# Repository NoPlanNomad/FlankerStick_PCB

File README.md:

# FlankerStick_PCBs
 
PCB's designed for my Flanker Style DIY Hotas stick.

https://cults3d.com/en/3d-model/game/flanker-style-stick

https://www.cgtrader.com/3d-print-models/hobby-diy/mechanical-parts/flanker-style-stick

# BOM
## GripLogic_FreeJoy
|quantaty | Type:Value      |Footprint|
|---------|-----------------|---------|
|2        |Capacitor : 0.1uF|0805     |
|9        |Resistor  : 1K   |0805     |
|2        |74HC165          |TSSOP-16 |
|2        |JST_XH:B5B-XH-A  |P2.50 mm |
|4        |JST_XH:B2B-XH-A  |P2.50 mm |
|2        |JST_XH:B7B-XH-A  |P2.50 mm |

## HeadLogic_FreeJoy
|quantaty | Type:Value      |Footprint|
|---------|-----------------|---------|
|3        |Capacitor : 0.1uF|0805     |
|24       |Resitor   : 1K   |0805     |
|3        |74HC165          |TSSOP-16 |
|4        |JST_XH:B7B-XH-A  |P2.50 mm |
|4        |JST_XH:B2B-XH-A  |P2.50 mm |
|1        |JST_XH:B5B-XH-A  |P2.50 mm |

## Breaklever_FreeJoy
|quantaty | Type:Value      |Footprint|
|---------|-----------------|---------|
|1        |SS495A           |TH       |
|1        |MCP3201          |SOIC 3.9 |
|1        |JST_XH:B5B-XH-A  |P2.50 mm |

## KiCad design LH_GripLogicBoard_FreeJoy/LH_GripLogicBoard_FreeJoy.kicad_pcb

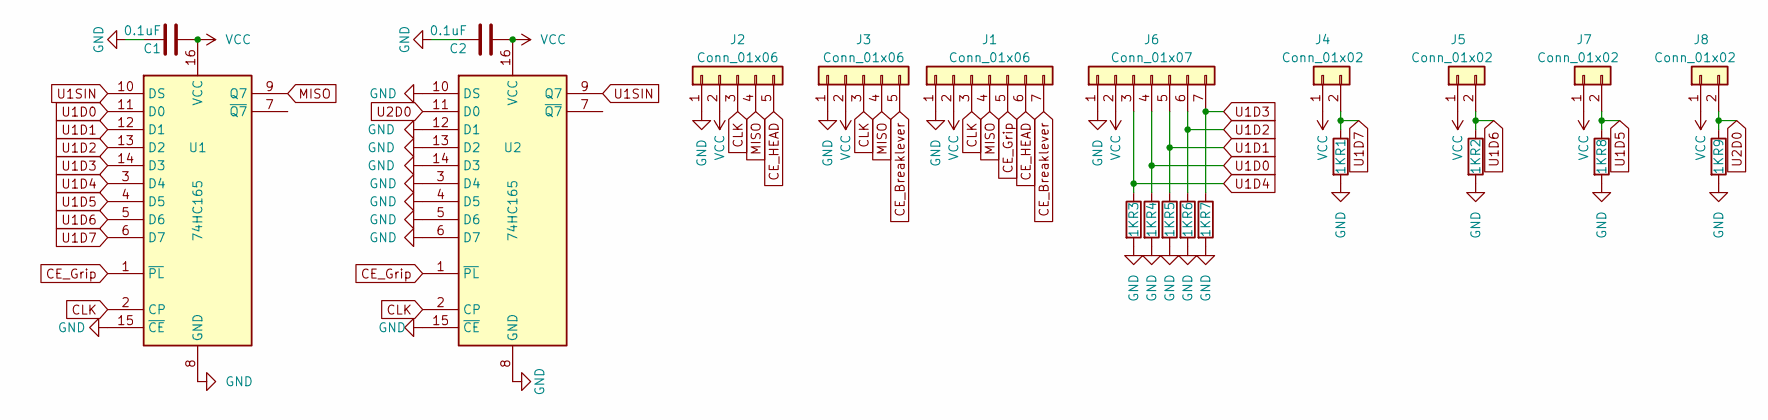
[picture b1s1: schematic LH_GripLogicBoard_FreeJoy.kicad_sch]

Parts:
C1, C2: 0.1uF; C_0805_2012Metric_Pad1.18x1.45mm_HandSolder
J1: Conn_01x06; JST_XH_B7B-XH-A_1x07_P2.50mm_Vertical
J2, J3: Conn_01x06; JST_XH_B5B-XH-A_1x05_P2.50mm_Vertical
J4, J5, J7, J8: Conn_01x02; JST_XH_B2B-XH-A_1x02_P2.50mm_Vertical
J6: Conn_01x07; JST_XH_B7B-XH-A_1x07_P2.50mm_Vertical
R1, R2, R3, R4, R5, R6, R7, R8, R9: 1K; R_0805_2012Metric_Pad1.20x1.40mm_HandSolder
U1, U2: 74HC165; TSSOP-16_4.4x5mm_P0.65mm

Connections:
CE_Breaklever: J1.7, J3.5
CE_Grip: J1.5, U1.1 (~PL), U2.1 (~PL)
CE_HEAD: J1.6, J2.5
CLK: J1.3, J2.3, J3.3, U1.2 (CP), U2.2 (CP)
GND: C1.1, C2.1, J1.1, J2.1, J3.1, J6.1, R1.2, R2.2, R3.2, R4.2, R5.2, R6.2, R7.2, R8.2, R9.2, U1.8 (GND), U1.15 (~CE), U2.3 (D4), U2.4 (D5), U2.5 (D6), U2.6 (D7), U2.8 (GND), U2.10 (DS), U2.12 (D1), U2.13 (D2), U2.14 (D3), U2.15 (~CE)
MISO: J1.4, J2.4, J3.4, U1.9 (Q7)
U1D0: J6.4, R4.1, U1.11 (D0)
U1D1: J6.5, R5.1, U1.12 (D1)
U1D2: J6.6, R6.1, U1.13 (D2)
U1D3: J6.7, R7.1, U1.14 (D3)
U1D4: J6.3, R3.1, U1.3 (D4)
U1D5: J7.2, R8.1, U1.4 (D5)
U1D6: J5.2, R2.1, U1.5 (D6)
U1D7: J4.2, R1.1, U1.6 (D7)
U1SIN: U1.10 (DS), U2.9 (Q7)
U2D0: J8.2, R9.1, U2.11 (D0)
VCC: C1.2, C2.2, J1.2, J2.2, J3.2, J4.1, J5.1, J6.2, J7.1, J8.1, U1.16 (VCC), U2.16 (VCC)

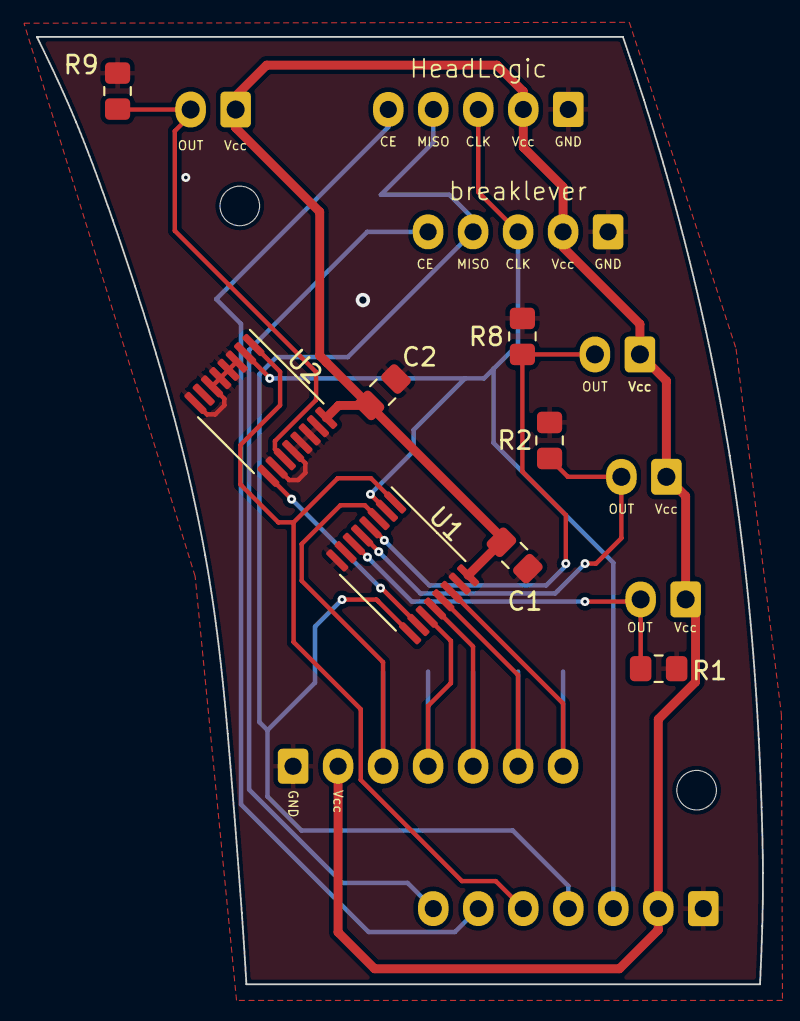
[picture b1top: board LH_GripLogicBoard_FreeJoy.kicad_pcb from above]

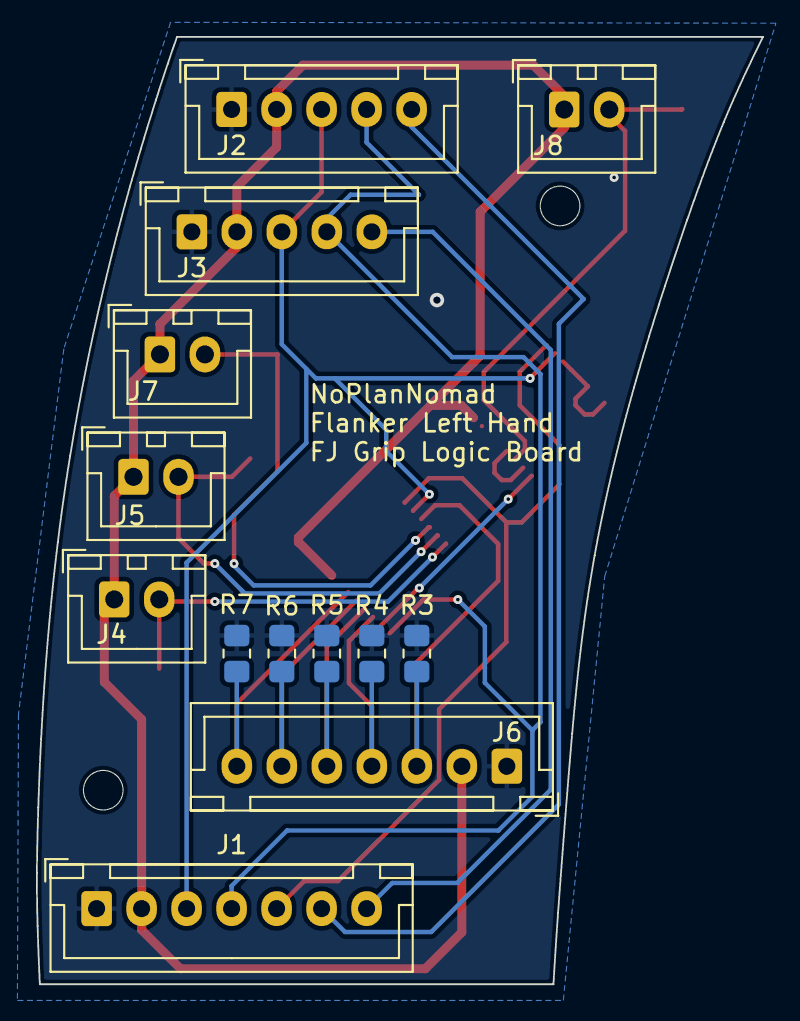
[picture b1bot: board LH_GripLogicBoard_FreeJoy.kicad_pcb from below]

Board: 2 copper layers, 40.3 x 52.6 mm, 21 parts (13 on the bottom side), 17 nets.

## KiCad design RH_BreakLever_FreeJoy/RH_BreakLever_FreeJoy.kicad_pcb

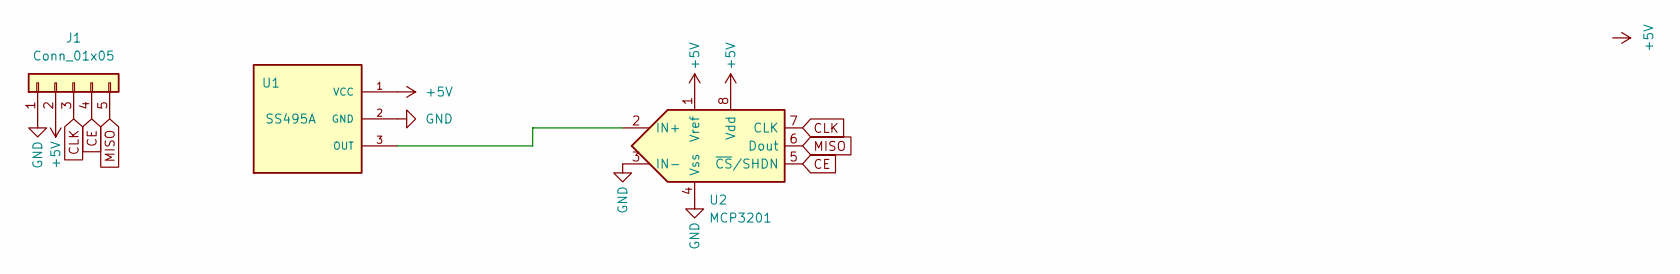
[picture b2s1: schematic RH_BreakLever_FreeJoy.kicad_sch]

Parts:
J1: Conn_01x05; JST_XH_B5B-XH-A_1x05_P2.50mm_Vertical
U1: SS495A; SS49E-T2; PARTREV Issue 3
U2: MCP3201; SOIC-8_3.9x4.9mm_P1.27mm

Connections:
+5V: J1.2, U1.1 (VCC), U2.1 (Vref), U2.8 (Vdd)
CE: J1.4, U2.5 (~CS/SHDN)
CLK: J1.3, U2.7 (CLK)
GND: J1.1, U1.2 (GND), U2.3 (IN-), U2.4 (Vss)
MISO: J1.5, U2.6 (Dout)
unnamed: U1.3 (OUT), U2.2 (IN+)

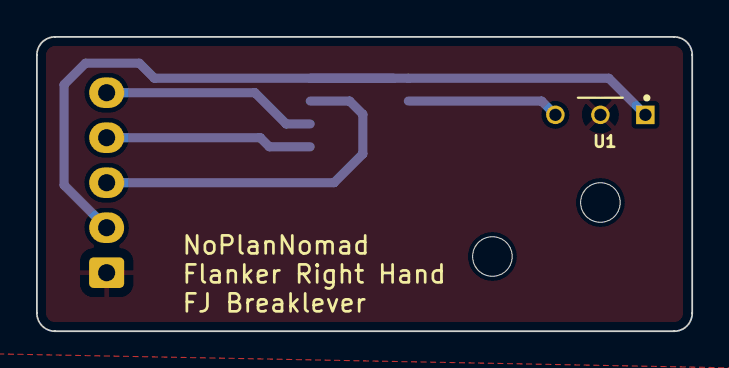
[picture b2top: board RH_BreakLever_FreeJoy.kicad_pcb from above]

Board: 2 copper layers, 36.4 x 16.3 mm, 5 parts (1 on the bottom side), 6 nets.

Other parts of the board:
M1, M2: MountingHole_2.2mm_M2

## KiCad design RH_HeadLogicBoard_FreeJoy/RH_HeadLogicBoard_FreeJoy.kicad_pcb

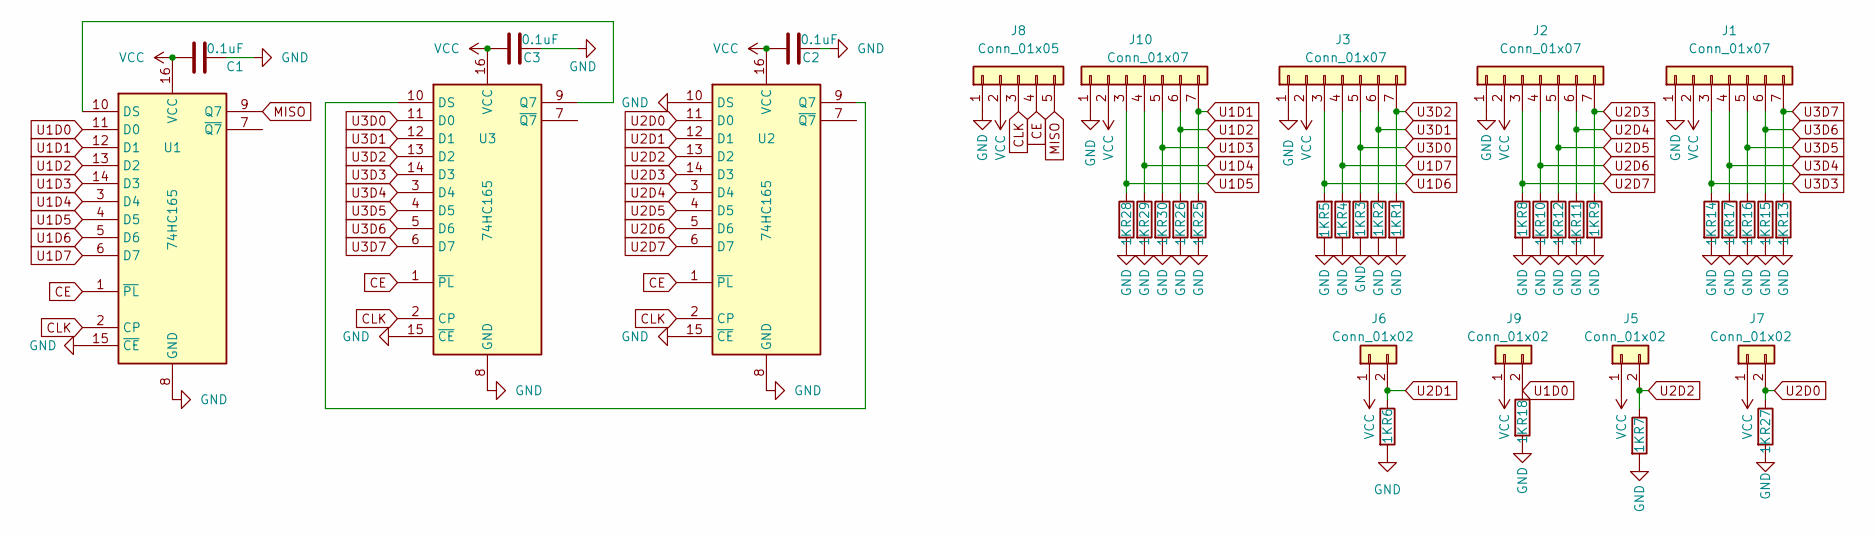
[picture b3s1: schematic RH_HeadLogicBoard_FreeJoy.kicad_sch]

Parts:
C1, C2, C3: 0.1uF; C_0805_2012Metric_Pad1.18x1.45mm_HandSolder
J1, J2, J3, J10: Conn_01x07; JST_XH_B7B-XH-A_1x07_P2.50mm_Vertical
J5, J6, J7, J9: Conn_01x02; JST_XH_B2B-XH-A_1x02_P2.50mm_Vertical
J8: Conn_01x05; JST_XH_B5B-XH-A_1x05_P2.50mm_Vertical
R1, R2, R3, R4, R5, R6, R7, R8, R9, R10, R11, R12, R13, R14, R15, R16, R17, R18, R25, R26, R27, R28, R29, R30: 1K; R_0805_2012Metric_Pad1.20x1.40mm_HandSolder
U1, U2, U3: 74HC165; TSSOP-16_4.4x5mm_P0.65mm

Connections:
+5V: C1.1, C2.1, C3.1, J1.2, J2.2, J3.2, J5.1, J6.1, J7.1, J8.2, J9.1, J10.2, U1.16 (VCC), U2.16 (VCC), U3.16 (VCC)
CE: J8.4, U1.1 (~PL), U2.1 (~PL), U3.1 (~PL)
CLK: J8.3, U1.2 (CP), U2.2 (CP), U3.2 (CP)
GND: C1.2, C2.2, C3.2, J1.1, J2.1, J3.1, J8.1, J10.1, R1.2, R2.2, R3.2, R4.1, R5.1, R6.2, R7.2, R8.2, R9.2, R10.2, R11.2, R12.2, R13.2, R14.2, R15.2, R16.2, R17.2, R18.2, R25.2, R26.2, R27.2, R28.2, R29.2, R30.2, U1.8 (GND), U1.15 (~CE), U2.8 (GND), U2.10 (DS), U2.15 (~CE), U3.8 (GND), U3.15 (~CE)
MISO: J8.5, U1.9 (Q7)
unnamed: U1.10 (DS), U3.9 (Q7)
unnamed: U2.9 (Q7), U3.10 (DS)
U1D0: J9.2, R18.1, U1.11 (D0)
U1D1: J10.7, R25.1, U1.12 (D1)
U1D2: J10.6, R26.1, U1.13 (D2)
U1D3: J10.5, R30.1, U1.14 (D3)
U1D4: J10.4, R29.1, U1.3 (D4)
U1D5: J10.3, R28.1, U1.4 (D5)
U1D6: J3.3, R5.2, U1.5 (D6)
U1D7: J3.4, R4.2, U1.6 (D7)
U2D0: J7.2, R27.1, U2.11 (D0)
U2D1: J6.2, R6.1, U2.12 (D1)
U2D2: J5.2, R7.1, U2.13 (D2)
U2D3: J2.7, R9.1, U2.14 (D3)
U2D4: J2.6, R11.1, U2.3 (D4)
U2D5: J2.5, R12.1, U2.4 (D5)
U2D6: J2.4, R10.1, U2.5 (D6)
U2D7: J2.3, R8.1, U2.6 (D7)
U3D0: J3.5, R3.1, U3.11 (D0)
U3D1: J3.6, R2.1, U3.12 (D1)
U3D2: J3.7, R1.1, U3.13 (D2)
U3D3: J1.3, R14.1, U3.14 (D3)
U3D4: J1.4, R17.1, U3.3 (D4)
U3D5: J1.5, R16.1, U3.4 (D5)
U3D6: J1.6, R15.1, U3.5 (D6)
U3D7: J1.7, R13.1, U3.6 (D7)

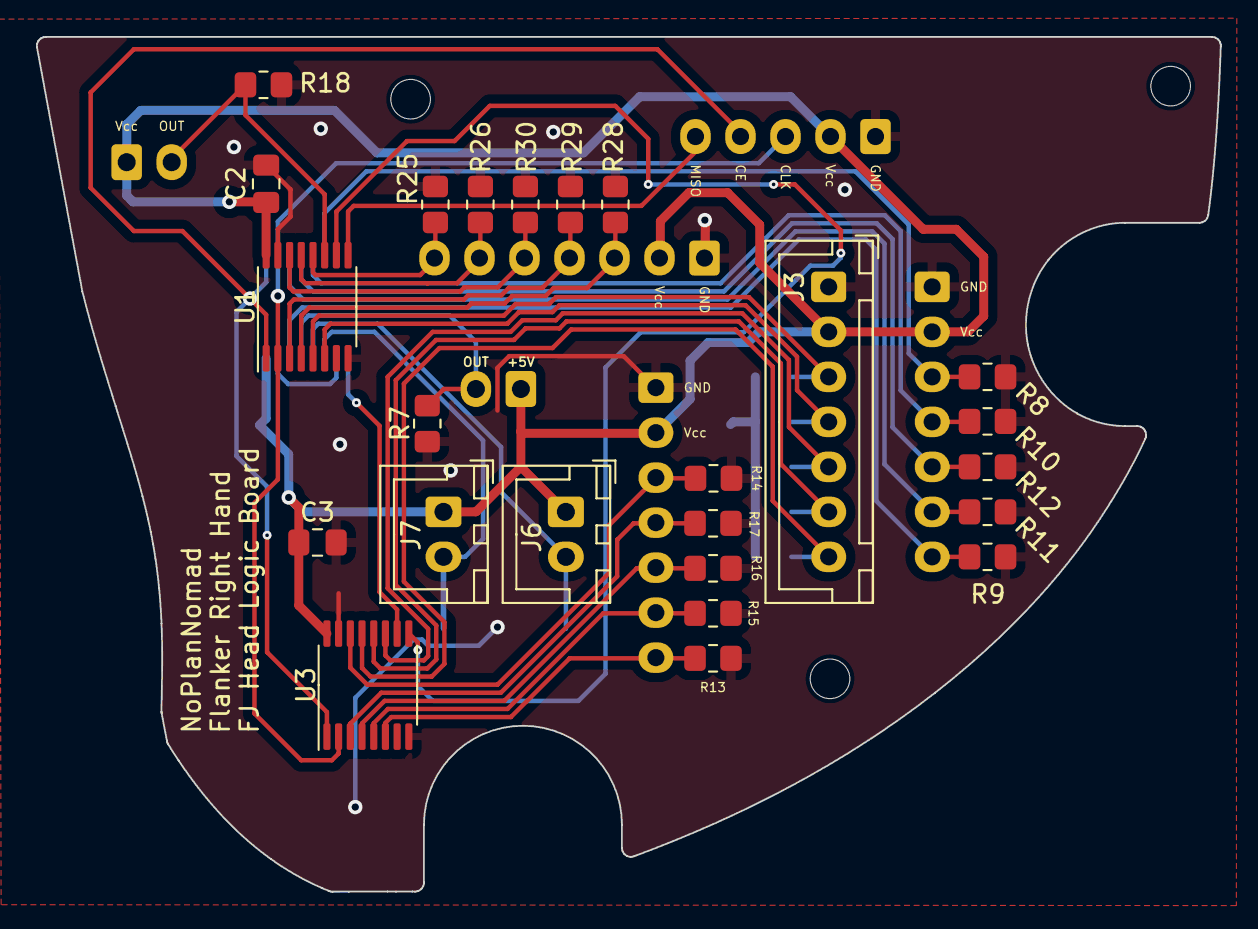
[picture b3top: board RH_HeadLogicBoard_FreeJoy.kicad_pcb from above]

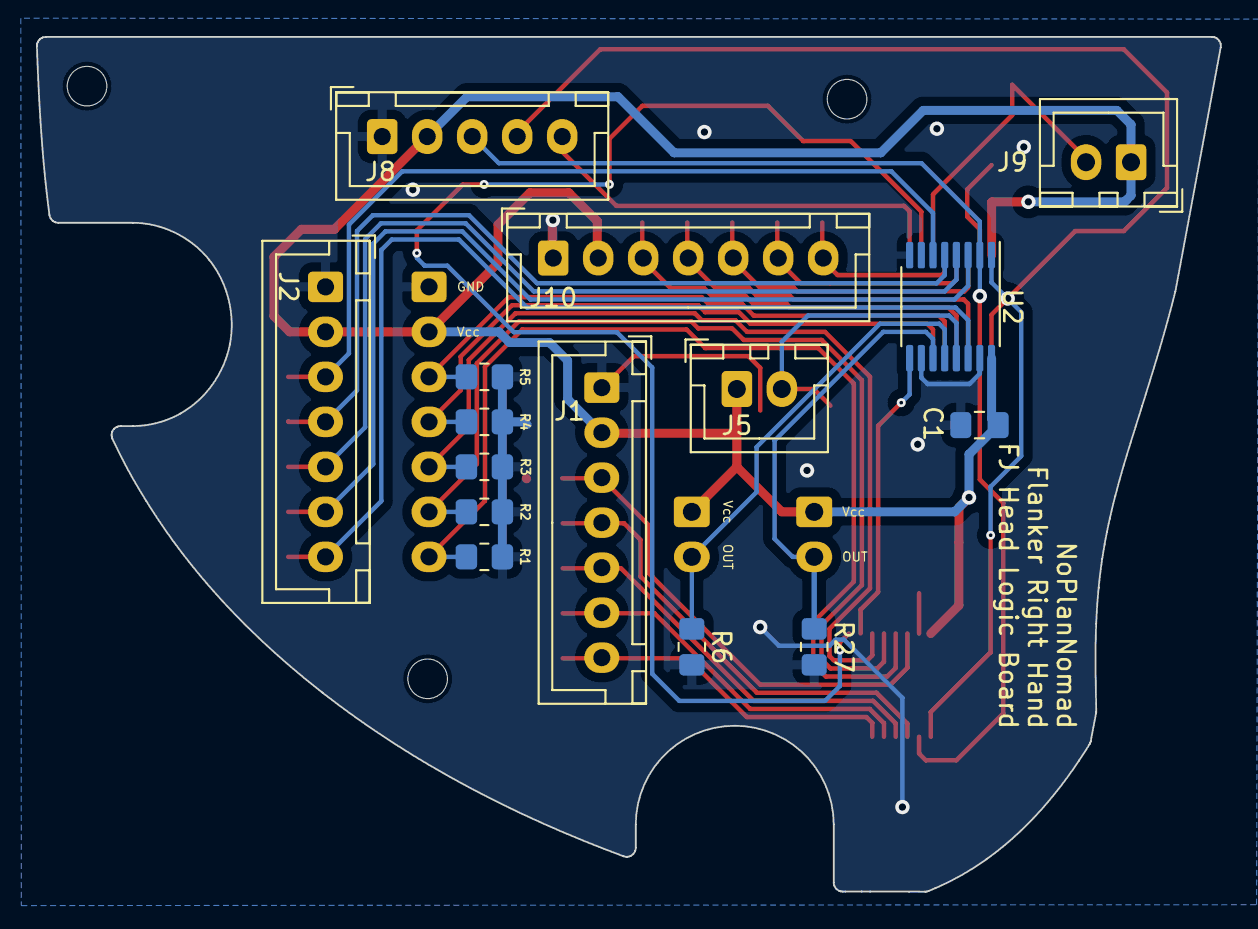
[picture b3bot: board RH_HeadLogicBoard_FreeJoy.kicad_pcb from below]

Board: 2 copper layers, 65.8 x 47.5 mm, 42 parts (15 on the bottom side), 31 nets.

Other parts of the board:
M1, M2, M3: MountingHole_2.2mm_M2

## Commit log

2023-07-13 added alps kicad submodule
2023-07-13 Update Alps_kicadlib
2023-07-13 library fix
2023-08-28 updated a footprint on Break-lever design for footprint naming.
2023-12-16 fixed mistake in Grip logic pcb's
2026-03-23 Fix quantity for JST_XH:B7B-XH-A in README.md
